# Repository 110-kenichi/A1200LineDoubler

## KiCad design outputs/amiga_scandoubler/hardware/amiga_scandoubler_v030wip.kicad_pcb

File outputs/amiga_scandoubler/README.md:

# Amiga 1200 15kHz → 31kHz スキャンダブラー

2026-09-29 / 全配線完了・製造データ一次版 v0.30 / **製造用リリースではありません（発注前の確認が残っている）**

## v0.30（最新）

- 変更点・検査結果・残作業：`revision_0.30.md`（作業ログは `revision_0.30wip.md`）
- 基板：`hardware/amiga_scandoubler_v030wip.kicad_pcb`（KiCad 7 形式。DRC エラー0・未接続0）
- 製造データ：`fab/v030wip/`（README に一覧と発注前の注意）
- 配線レビューとシミュレーション：`review_v030wip_wiring.md`
- ERC：`hardware/erc_k9.rpt`、除外 `hardware/erc_exclusions.json`

## v0.27 の内容（以下は当時の記述）

- **最新：出力側H/V同期配線**：`sync_out_review.md`
- 現行基板：`hardware/amiga_scandoubler_sync_out.kicad_pcb`
- 独立検査：`hardware/sync_out_report.json`、`hardware/sync_out_drc.txt`
- 配線図：`sync_out_review.png`、`sync_out_detail.png`

- v0.26：DACのRGB出力接続：`rgb_out_review.md`
- v0.26基板：`hardware/amiga_scandoubler_rgb_out.kicad_pcb`
- 検査：`hardware/rgb_out_report.json`、`hardware/rgb_out_drc.txt`
- 配線図：`rgb_out_review.png`、`rgb_out_detail.png`

- v0.25：PLLフィルター表面配線：`pll_top_review.md`
- v0.25基板：`hardware/amiga_scandoubler_pll_top.kicad_pcb`
- 独立検査：`hardware/pll_top_report.json`、`hardware/pll_top_drc.txt`
- 配線図：`pll_top_review.png`、`pll_top_detail.png`

- v0.24：R34付近の電源配線見直し：`r34_review.md`
- v0.24基板：`hardware/amiga_scandoubler_refined.kicad_pcb`
- 検査：`hardware/refined_report.json`、`hardware/refined_drc.txt`
- 配線図：`refined_review.png`

- v0.23：アナログ信号の部分配線：`analog_review.md`
- v0.23基板：`hardware/amiga_scandoubler_analog.kicad_pcb`
- 独立検査：`hardware/analog_report.json`、`hardware/analog_drc.txt`
- 配線図：`analog_review.png`、`analog_detail.png`

- v0.22：主要ICへの電源分配：`distribution_review.md`
- v0.22基板：`hardware/amiga_scandoubler_distribution.kicad_pcb`
- 接続・間隔の検査：`hardware/distribution_report.json`、`hardware/distribution_drc.txt`
- 主要IC周辺の配線図：`distribution_detail.png`

- v0.21 電源部の部分配線：`power_routing_review.md`
- v0.21の部分配線基板：`hardware/amiga_scandoubler_routing.kicad_pcb`
- 電源部の拡大図：`power_routing_detail.png`
- 接続・DRC検査：`hardware/power_routing_report.json`、`hardware/power_routing_drc.txt`

- FPGA現行：出力リセット解除の同期化：`output_release_review.md`
- 現行実装・経路解析・再現手順：`implementation/output_release/`

- v0.19 DAC出力段同期化：`output_stage_review.md`
- v0.19の再合成・配置配線と解析：`implementation/output_stage/`

- 出力段追加前のDACタイミング調査：`dac_timing_review.md`
- 端子別の暫定条件と解析手順：`implementation/dac_timing_budget.json`、`implementation/analyze_dac_sdf.py`

- PLLを180度へ更新：`phase180_integration.md`
- 180度の再合成・配置配線・遅延解析：`implementation/phase180/`
- 更新後の試験：`system_phase180_report.txt`、`capture_phase180_current_report.txt`

- 旧90度設定の調査履歴：`capture_timing_review.md`
- 配置後52経路の暫定解析：`implementation/capture_timing_estimate.json`
- 90度／180度の機能試験：`capture_phase90_report.txt`、`capture_phase180_report.txt`

- FPGA配置配線の試行結果と検証限界：`implementation_review.md`
- 配置配線後の回路・ログ・周期制約・再現手順：`implementation/`

- 基板トップの合成・合成後リセット検証：`board_synthesis.md`
- 合成後接続の照合：`board_netlist_audit.txt`、`synthesis/board_summary.json`
- 合成後リセット試験：`mapped_reset_simulation_report.txt`

- 基板接続と端子修正：`board_integration.md`、`rtl/amiga_board_top.sv`
- 62信号の端子制約候補：`constraints/amiga_board_top.cst`、`constraints/board_port_map.json`
- 起動リセット候補と試験：`rtl/configuration_reset.sv`、`board_simulation_report.txt`

- 統合回路の合成結果：`system_synthesis.md`、`synthesis/system_summary.json`
- 1816/2048条件の合成手順・ログ・ネットリスト：`synthesis/system_*`

- 機能回路の全体接続：`system_integration.md`、`rtl/amiga_logic_core.sv`
- ADC起動から映像出力までの機能試験：`system_simulation_report.txt`

- PLL再起動と監視接続：`pll_restart.md`、`rtl/pll_restart_control.sv`、`rtl/clock_recovery_system.sv`
- 起動・復帰の試験記録：`pll_restart_simulation_report.txt`

- PLL設定・ADC入力レジスターの構成候補：`pll_capture.md`、`rtl/gowin_video_pll.sv`、`rtl/adc_rgb_capture.sv`
- 理想クロックによる取り込み試験：`capture_simulation_report.txt`

- 入力同期前段と映像処理への接続：`stream_input.md`、`rtl/stream_sync_frontend.sv`、`rtl/stream_input_video.sv`
- 前段・統合試験の記録：`stream_simulation_report.txt`

- ADCの36件の設定候補と起動統合：`adc_configuration.md`、`rtl/tvp7002_boot.sv`
- ADC起動統合の試験結果：`adc_boot_simulation_report.txt`

- クロック停止監視・DAC省電力制御の接続条件：`clock_integration.md`
- 監視回路と統合映像処理：`rtl/video_clock_guard.sv`、`rtl/supervised_video_core.sv`
- 新規試験結果：`clock_simulation_report.txt`

- RGB・HS・VSを整列した統合映像処理：`rtl/video_core.sv`
- 統合試験の結果：`video_simulation_report.txt`
- 専用RAMへの合成確認：`synthesis_review.md`、`synthesis/`

- 合意済み仕様と回路構成案：`design.md`
- 編集可能なKiCad 7回路図（6機能シート）：`hardware/amiga_scandoubler.kicad_sch`
- 閲覧用の回路図（7ページ）：`schematic_review.pdf`
- 135部品・129接続の定義：`hardware/circuit_manifest.json`
- FPGAの仮端子割り当て：`hardware/fpga_pin_assignment.json`
- KiCad出力ネットリスト：`hardware/amiga_scandoubler.net`
- 接続照合の結果：`hardware/connectivity_report.txt`
- この版の変更点と残作業：`revision_0.27.md`
- 95×95mm・全135部品の配置基板：`hardware/amiga_scandoubler_placement.kicad_pcb`（未配線）
- 配置図：`placement_review.png`、`placement_review.svg`
- パッド接続・部品外形の照合：`hardware/placement_report.json`
- FPGA・ADCの専用フットプリント：`hardware/Amiga.pretty/`
- フットプリントの確認記録：`hardware/footprint_review.md`
- ADC起動制御・I²C通信：`rtl/adc_power_sequence.sv`、`rtl/i2c_register_write.sv`
- 制御系の接続条件：`control_interface.md`、試験結果：`control_simulation_report.txt`
- メーカー資料に基づく入力回路・端子接続案：`input_circuit.md`
- 主要部品の選定・調達確認状況：`parts_review.md`
- ライン倍化のSystemVerilog処理核：`rtl/line_double.sv`
- フィールド単位の出力同期処理核：`rtl/field_sync.sv`
- 自動照合付きシミュレーション：`sim/`、実行結果：`simulation_report.txt`
- 実機での確認項目と製造データの完成条件：`verification.md`

現在のコードは、ADC起動から映像出力までの機能回路を接続した**検証版**です。基板トップと実PLL・DDR出力の接続候補を追加しましたが、実入力設定、DACタイミング、端子の実配置まで検証した製品用FPGAデータではありません。

回路図と4層基板は検討版です。現行基板には電源部の部分配線と内層GND面がありますが、未接続160件とシルクの問題が残り、基板全体のDRCは合格していません。ガーバー、完成BOM、CPL、書き込み用ビットストリームは未作成です。フットプリントには寸法・実装条件の確認が残るものがあります。この版をJLCPCBに提出しないでください。

KiCadで開くときは`hardware`フォルダーをまとめて展開し、`amiga_scandoubler.kicad_sch`を開いてください。子シートとローカルシンボルも同梱しています。接続検査はKiCadが実際に出力したデータを照合しました。ERC、基板DRC、基板全体の合成・配置配線、実機試験の合格を意味するものではありません。

## 合意済み条件

Amiga 1200、所有済みのUNBUFFERED VGA変換アダプター、BENQ GW2780を使用。基板の入出力はいずれも3列15ピンDE-15メス。USB給電。15kHzのPAL/NTSCプログレッシブおよびインターレースを2倍の水平周波数に変換。インターレースはBob方式、各フィールドを1出力フレームにする。低遅延を優先し、外付けフレームメモリ・動き適応・フレームレート変換は搭載しない。

基板は100×100mm以内を目標とし、配線品質や実装性を優先する。今回の配置案は95×95mm。これは基板外形であり、コネクターや接続ケーブルを含む外形ではない。

## 検証の再実行

Python 3とIcarus Verilogを用意して、次を実行します。

```text
python sim/run_tests.py --bin-dir <Icarusのbinフォルダー> --report simulation_report.txt
python sim/run_control_tests.py --bin-dir <Icarusのbinフォルダー> --report control_simulation_report.txt
python sim/run_video_tests.py --bin-dir <Icarusのbinフォルダー> --report video_simulation_report.txt
python sim/run_clock_tests.py --bin-dir <Icarusのbinフォルダー> --report clock_simulation_report.txt
python sim/run_adc_boot_tests.py --bin-dir <Icarusのbinフォルダー> --report adc_boot_simulation_report.txt
python sim/run_stream_tests.py --bin-dir <Icarusのbinフォルダー> --report stream_simulation_report.txt
python sim/run_capture_tests.py --bin-dir <Icarusのbinフォルダー> --report capture_simulation_report.txt
python sim/run_pll_restart_tests.py --bin-dir <Icarusのbinフォルダー> --report pll_restart_simulation_report.txt
python sim/run_system_tests.py --bin-dir <Icarusのbinフォルダー> --report system_simulation_report.txt
python sim/run_board_tests.py --bin-dir <Icarusのbinフォルダー> --report board_simulation_report.txt
```

シミュレーションは処理核のデジタル動作を確認します。Amiga実機、アナログ画質、モニター互換性、FPGAへの実装可能性や実測遅延の確認ではありません。

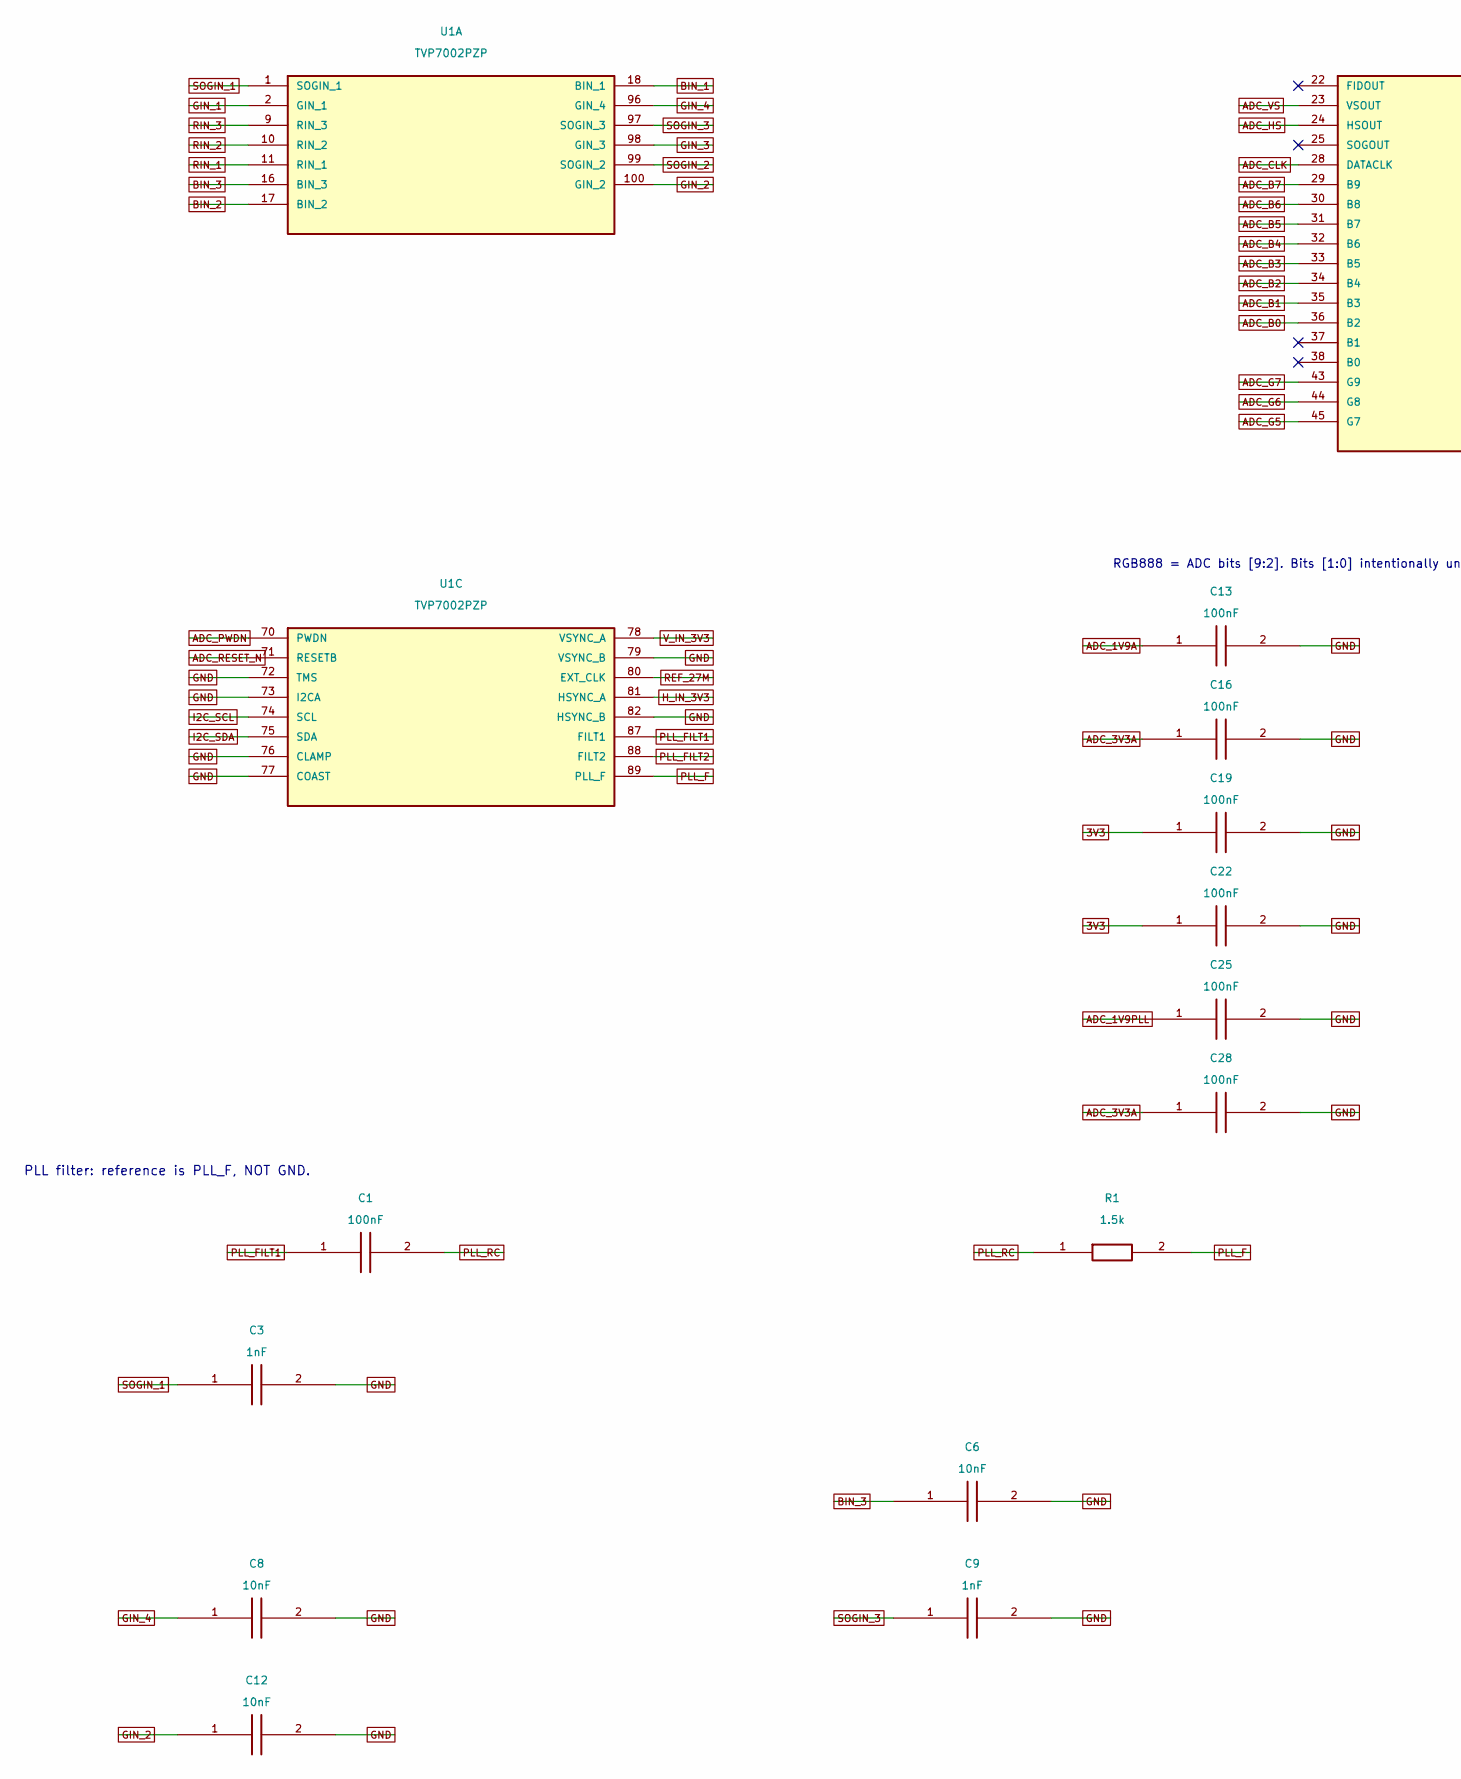
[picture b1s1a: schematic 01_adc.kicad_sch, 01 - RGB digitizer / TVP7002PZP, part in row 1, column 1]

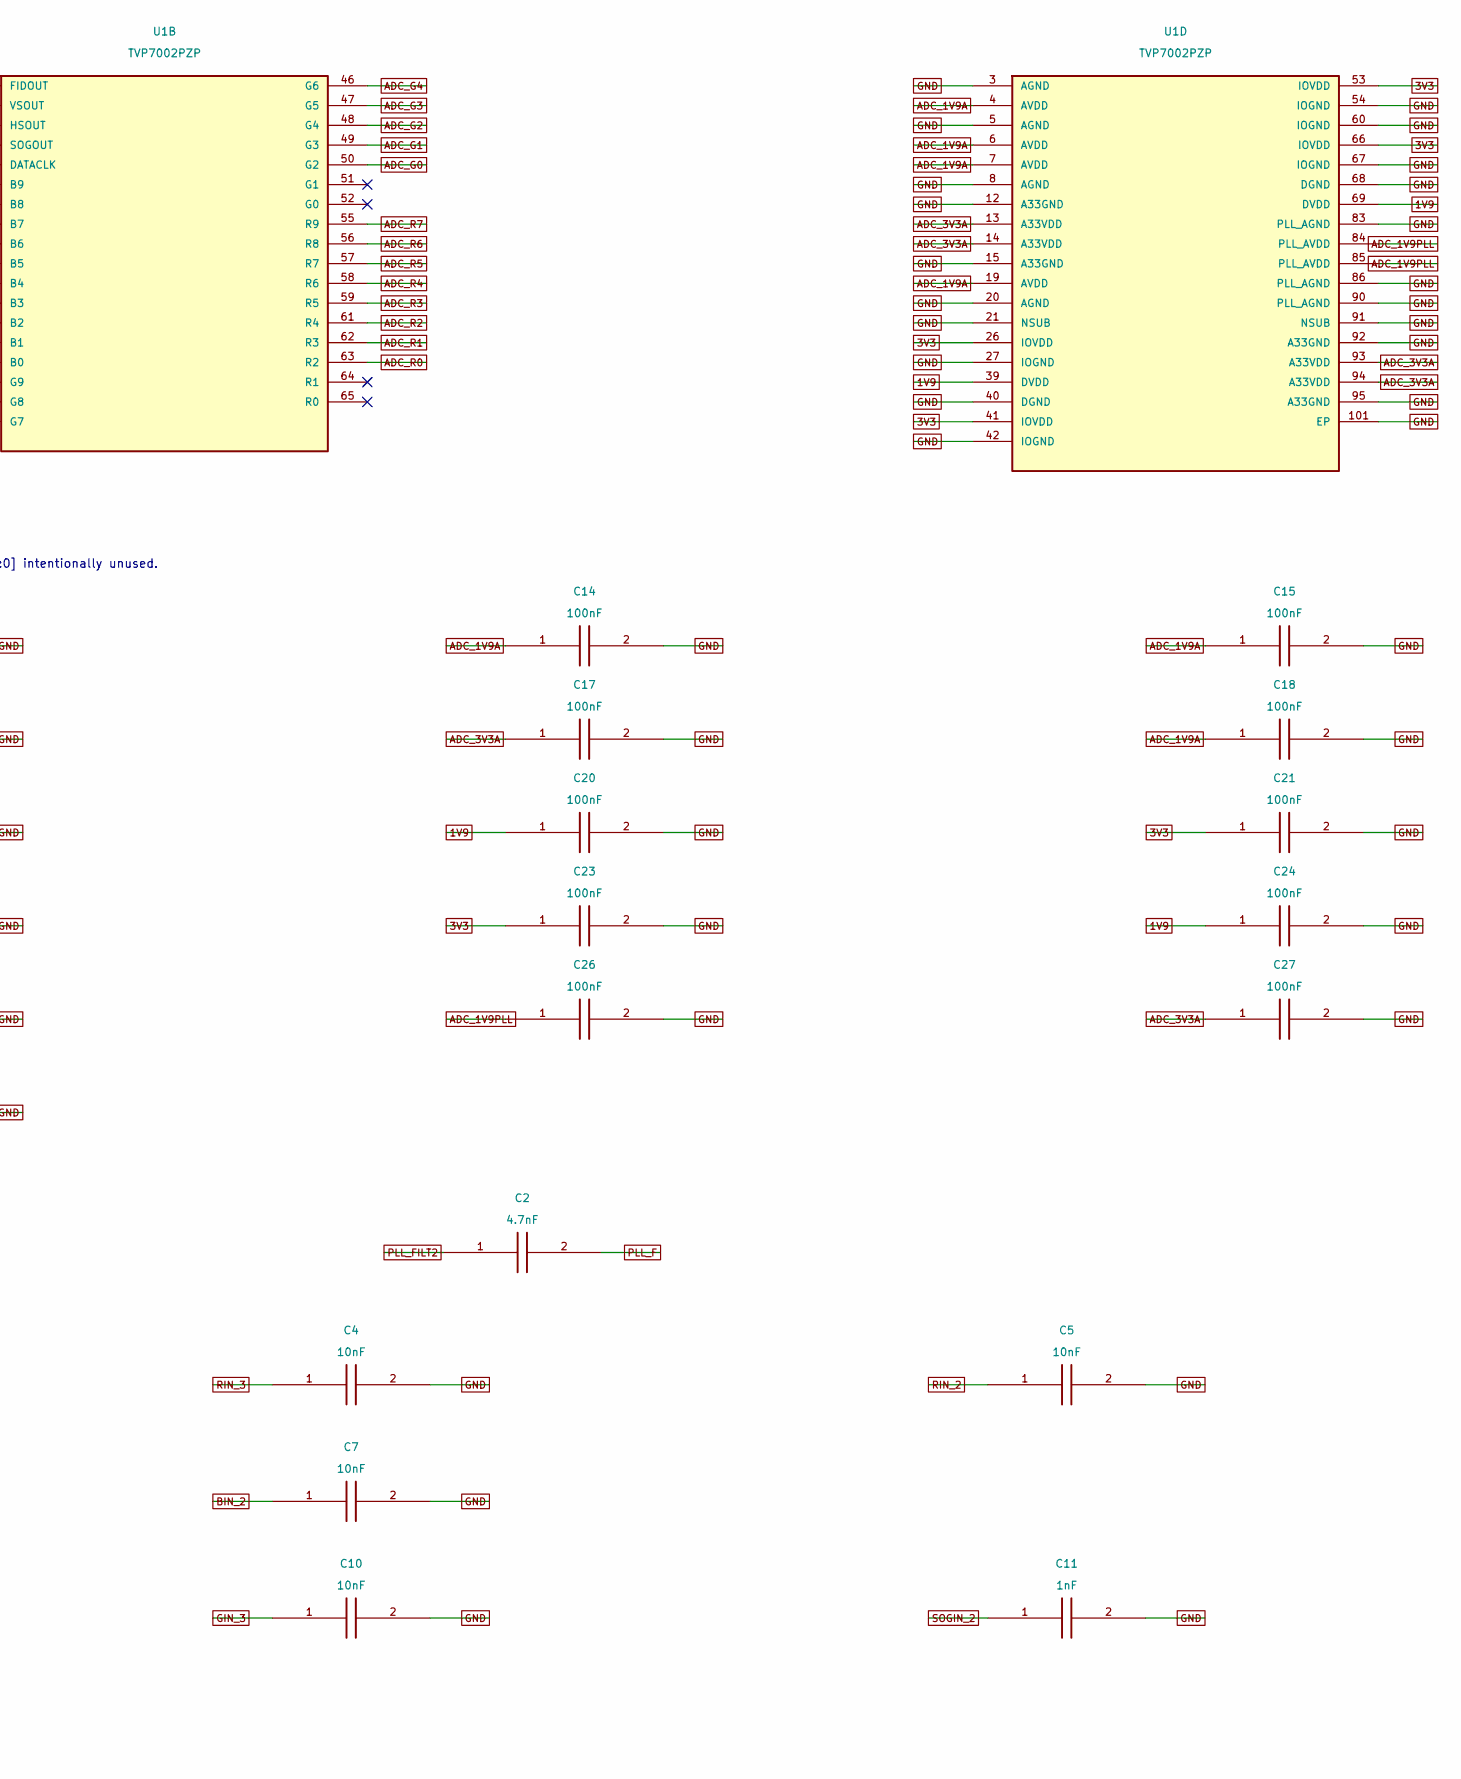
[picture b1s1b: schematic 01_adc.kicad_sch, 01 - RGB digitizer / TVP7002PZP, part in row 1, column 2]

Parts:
C1, C13, C14, C15, C16, C17, C18, C19, C20, C21, C22, C23, C24, C25, C26, C27, C28: 100nF; C_0603_1608Metric; MPN CC0603KRX7R9BB104; LCSC C14663
C2: 4.7nF; C_0603_1608Metric; MPN CC0603JRNPO9BN472; LCSC C576818
C3, C9, C11: 1nF; C_0603_1608Metric; MPN CC0603JRNPO9BN102; LCSC C106246
C4, C5, C6, C7, C8, C10, C12: 10nF; C_0603_1608Metric; MPN GRM1885C1H103JA01D; LCSC C85973
R1: 1.5k; R_0603_1608Metric; MPN 0603WAF1501T5E; LCSC C22843
U1: TVP7002PZP; TQFP-100_TVP7002_14x14_P0.5_EP6.2; MPN TVP7002PZP; LCSC C3824085

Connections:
1V9: C20.1, C24.1, U1.39 (DVDD), U1.69 (DVDD); also elsewhere on the board
3V3: C19.1, C21.1, C22.1, C23.1, U1.26 (IOVDD), U1.41 (IOVDD), U1.53 (IOVDD), U1.66 (IOVDD); also elsewhere on the board
ADC_1V9A: C13.1, C14.1, C15.1, C18.1, U1.4 (AVDD), U1.6 (AVDD), U1.7 (AVDD), U1.19 (AVDD); also elsewhere on the board
ADC_1V9PLL: C25.1, C26.1, U1.84 (PLL_AVDD), U1.85 (PLL_AVDD); also elsewhere on the board
ADC_3V3A: C16.1, C17.1, C27.1, C28.1, U1.13 (A33VDD), U1.14 (A33VDD), U1.93 (A33VDD), U1.94 (A33VDD); also elsewhere on the board
ADC_B0: U1.36 (B2); also elsewhere on the board
ADC_B1: U1.35 (B3); also elsewhere on the board
ADC_B2: U1.34 (B4); also elsewhere on the board
ADC_B3: U1.33 (B5); also elsewhere on the board
ADC_B4: U1.32 (B6); also elsewhere on the board
ADC_B5: U1.31 (B7); also elsewhere on the board
ADC_B6: U1.30 (B8); also elsewhere on the board
ADC_B7: U1.29 (B9); also elsewhere on the board
ADC_CLK: U1.28 (DATACLK); also elsewhere on the board
ADC_G0: U1.50 (G2); also elsewhere on the board
ADC_G1: U1.49 (G3); also elsewhere on the board
ADC_G2: U1.48 (G4); also elsewhere on the board
ADC_G3: U1.47 (G5); also elsewhere on the board
ADC_G4: U1.46 (G6); also elsewhere on the board
ADC_G5: U1.45 (G7); also elsewhere on the board
ADC_G6: U1.44 (G8); also elsewhere on the board
ADC_G7: U1.43 (G9); also elsewhere on the board
ADC_HS: U1.24 (HSOUT); also elsewhere on the board
ADC_PWDN: U1.70 (PWDN); also elsewhere on the board
ADC_R0: U1.63 (R2); also elsewhere on the board
ADC_R1: U1.62 (R3); also elsewhere on the board
ADC_R2: U1.61 (R4); also elsewhere on the board
ADC_R3: U1.59 (R5); also elsewhere on the board
ADC_R4: U1.58 (R6); also elsewhere on the board
ADC_R5: U1.57 (R7); also elsewhere on the board
ADC_R6: U1.56 (R8); also elsewhere on the board
ADC_R7: U1.55 (R9); also elsewhere on the board
ADC_RESET_N: U1.71 (RESETB); also elsewhere on the board
ADC_VS: U1.23 (VSOUT); also elsewhere on the board
BIN_1: U1.18 (BIN_1); also elsewhere on the board
BIN_2: C7.1, U1.17 (BIN_2)
BIN_3: C6.1, U1.16 (BIN_3)
GIN_1: U1.2 (GIN_1); also elsewhere on the board
GIN_2: C12.1, U1.100 (GIN_2)
GIN_3: C10.1, U1.98 (GIN_3)
GIN_4: C8.1, U1.96 (GIN_4)
GND: C3.2, C4.2, C5.2, C6.2, C7.2, C8.2, C9.2, C10.2, C11.2, C12.2, C13.2, C14.2, C15.2, C16.2, C17.2, C18.2, C19.2, C20.2, C21.2, C22.2, C23.2, C24.2, C25.2, C26.2, C27.2, C28.2, U1.3 (AGND), U1.5 (AGND), U1.8 (AGND), U1.12 (A33GND), U1.15 (A33GND), U1.20 (AGND), U1.21 (NSUB), U1.27 (IOGND), U1.40 (DGND), U1.42 (IOGND), U1.54 (IOGND), U1.60 (IOGND), U1.67 (IOGND), U1.68 (DGND), U1.72 (TMS), U1.73 (I2CA), U1.76 (CLAMP), U1.77 (COAST), U1.79 (VSYNC_B), U1.82 (HSYNC_B), U1.83 (PLL_AGND), U1.86 (PLL_AGND), U1.90 (PLL_AGND), U1.91 (NSUB), U1.92 (A33GND), U1.95 (A33GND), U1.101 (EP); also elsewhere on the board
H_IN_3V3: U1.81 (HSYNC_A); also elsewhere on the board
I2C_SCL: U1.74 (SCL); also elsewhere on the board
I2C_SDA: U1.75 (SDA); also elsewhere on the board
PLL_F: C2.2, R1.2, U1.89 (PLL_F)
PLL_FILT1: C1.1, U1.87 (FILT1)
PLL_FILT2: C2.1, U1.88 (FILT2)
PLL_RC: C1.2, R1.1
REF_27M: U1.80 (EXT_CLK); also elsewhere on the board
RIN_1: U1.11 (RIN_1); also elsewhere on the board
RIN_2: C5.1, U1.10 (RIN_2)
RIN_3: C4.1, U1.9 (RIN_3)
SOGIN_1: C3.1, U1.1 (SOGIN_1)
SOGIN_2: C11.1, U1.99 (SOGIN_2)
SOGIN_3: C9.1, U1.97 (SOGIN_3)
V_IN_3V3: U1.78 (VSYNC_A); also elsewhere on the board

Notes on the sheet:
RGB888 = ADC bits [9:2]. Bits [1:0] intentionally unused.
PLL filter: reference is PLL_F, NOT GND.

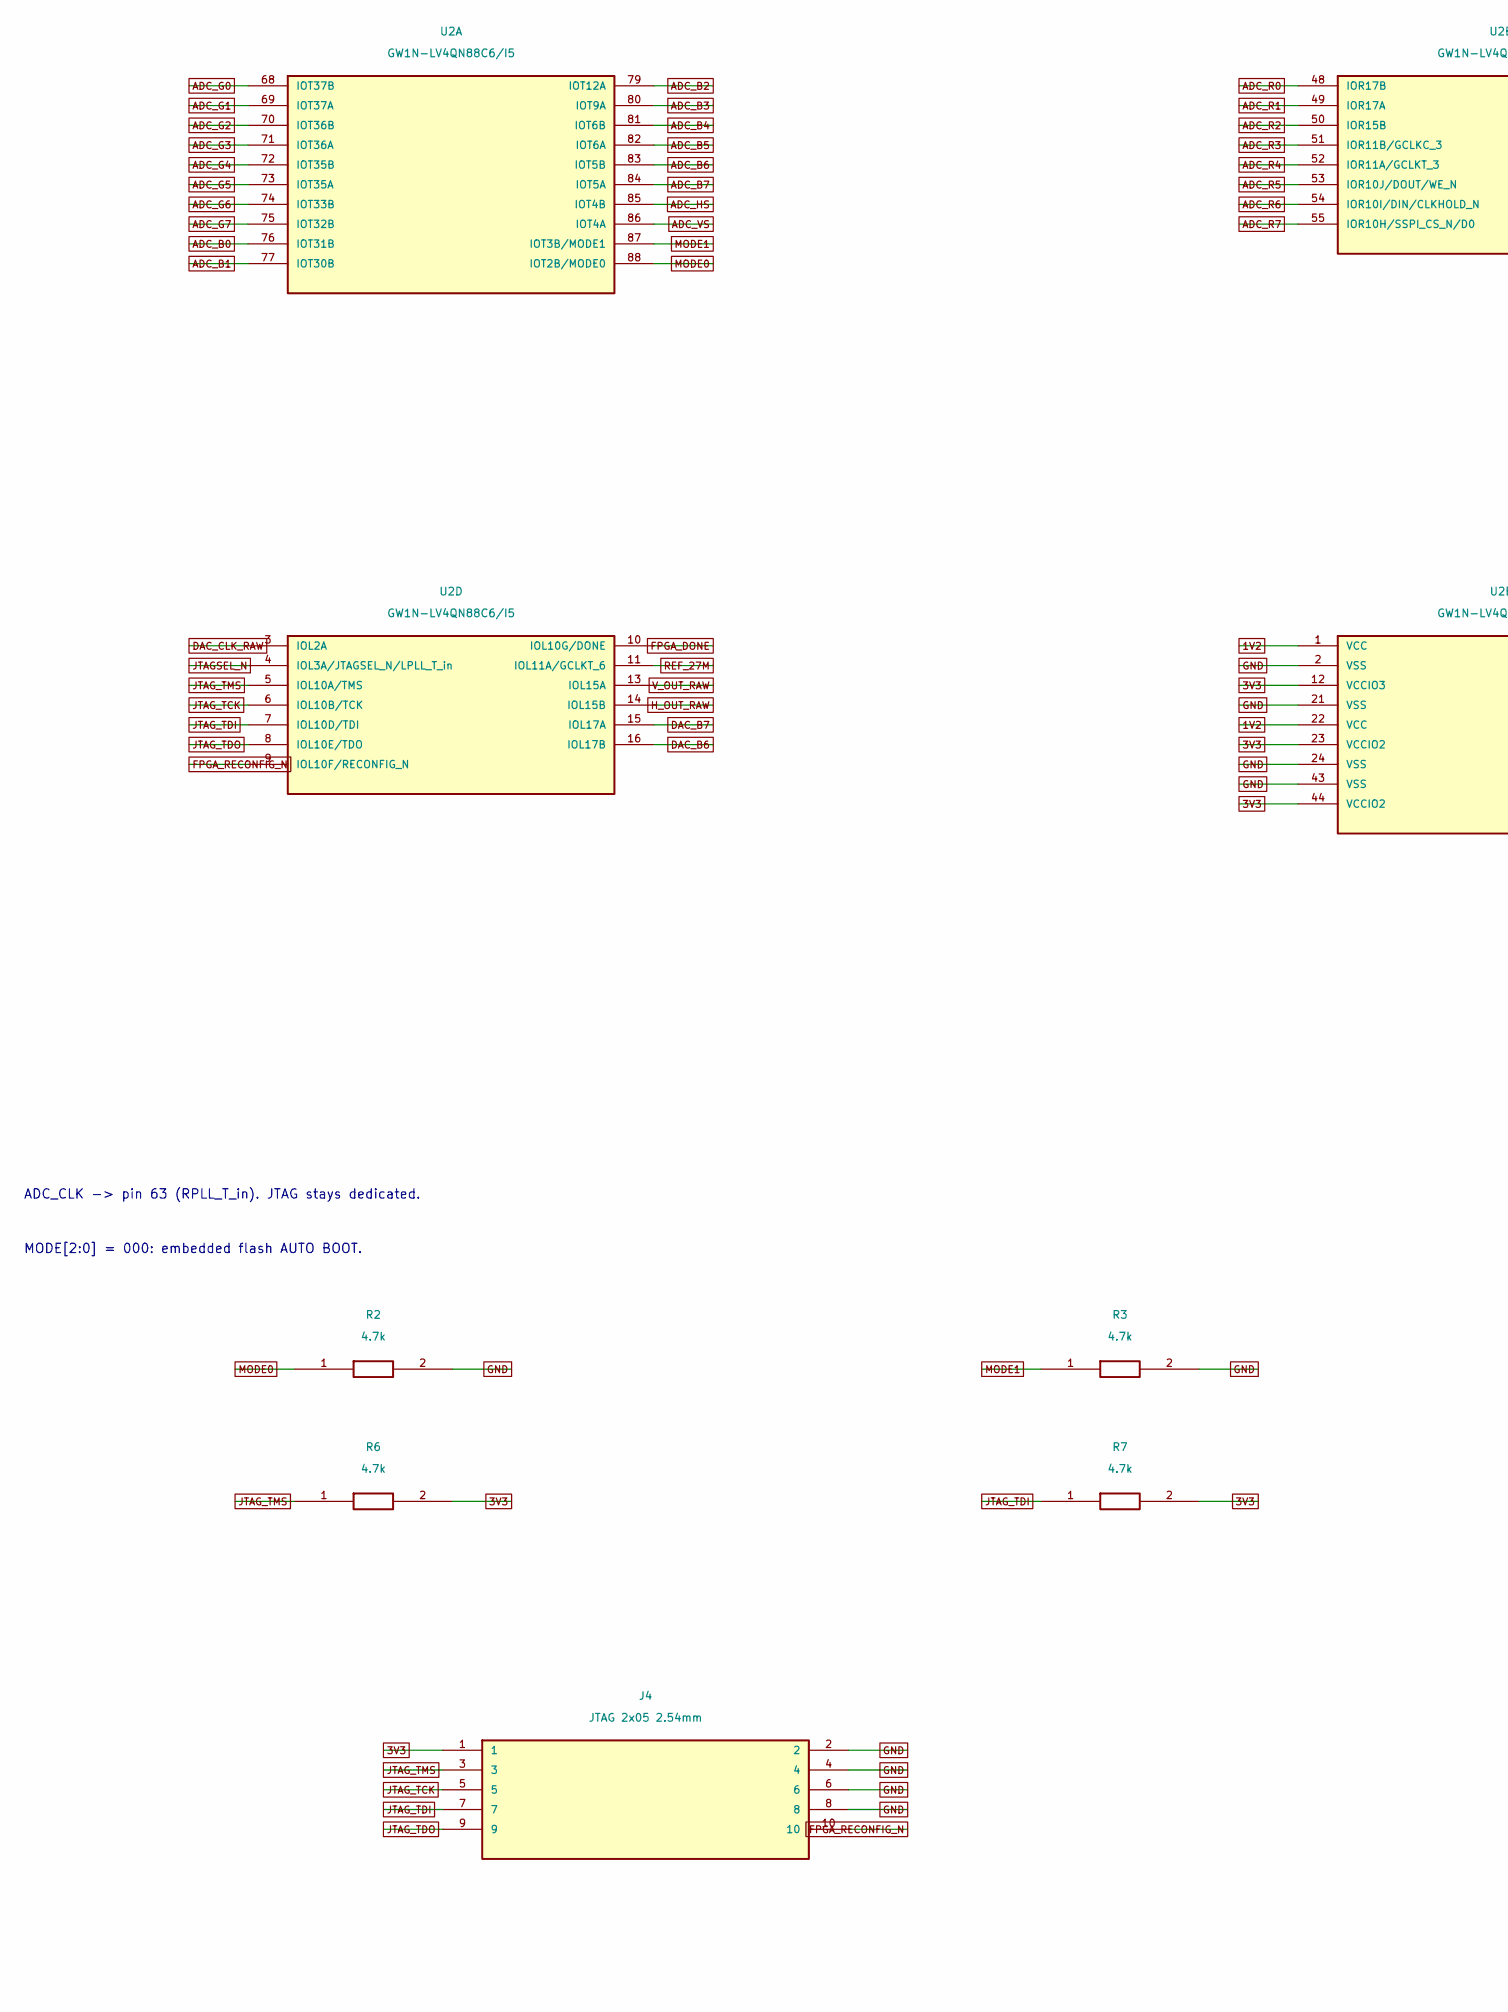
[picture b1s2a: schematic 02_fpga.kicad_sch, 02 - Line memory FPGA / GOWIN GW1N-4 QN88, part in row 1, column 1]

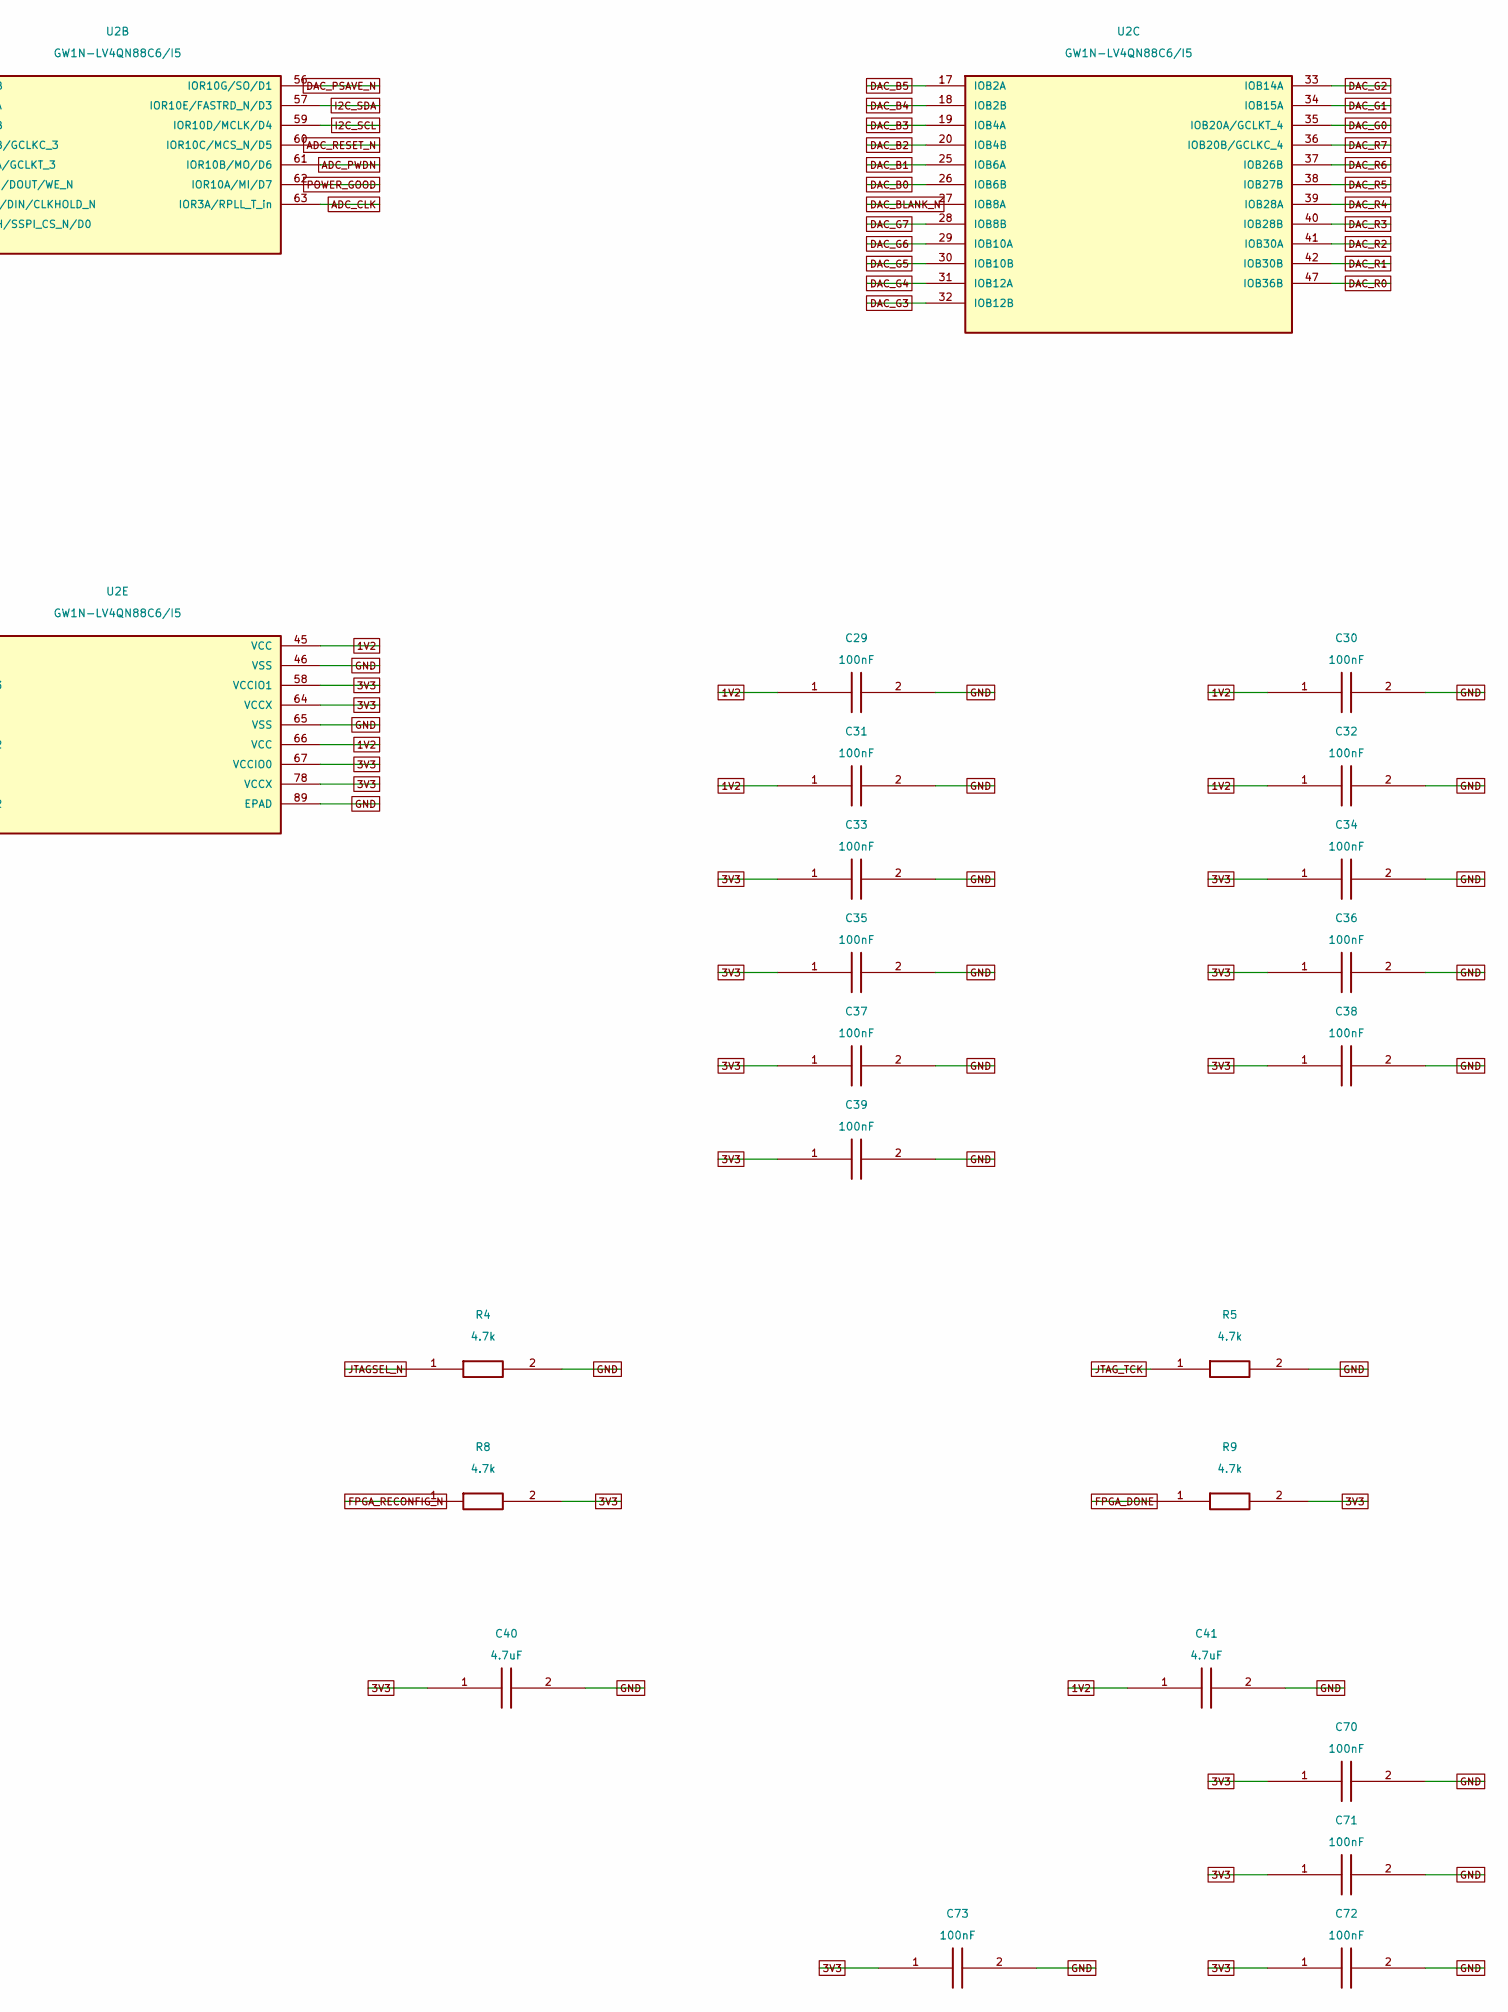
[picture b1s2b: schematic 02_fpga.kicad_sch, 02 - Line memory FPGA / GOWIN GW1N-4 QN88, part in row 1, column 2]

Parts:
C29, C30, C31, C32, C33, C34, C35, C36, C37, C38, C39: 100nF; C_0603_1608Metric; MPN CC0603KRX7R9BB104; LCSC C14663
C40, C41: 4.7uF; C_0805_2012Metric; MPN CL21A475KAQNNNE; LCSC C1779
C70, C71, C72, C73: 100nF; C_0402_1005Metric; MPN CL05B104KO5NNNC; LCSC C1525
J4: JTAG 2x05 2.54mm; PinHeader_2x05_P2.54mm_Vertical_SMD; MPN HX PZ2.54-2x5P TP; LCSC C32713285
R2, R3, R4, R5, R6, R7, R8, R9: 4.7k; R_0603_1608Metric; MPN 0603WAF4701T5E; LCSC C23162
U2: GW1N-LV4QN88C6/I5; QFN-88_GW1N4_10x10_P0.4_EP6.8; MPN GW1N-LV4QN88C6/I5; LCSC C31900351

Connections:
1V2: C29.1, C30.1, C31.1, C32.1, C41.1, U2.1 (VCC), U2.22 (VCC), U2.45 (VCC), U2.66 (VCC); also elsewhere on the board
3V3: C33.1, C34.1, C35.1, C36.1, C37.1, C38.1, C39.1, C40.1, C70.1, C71.1, C72.1, C73.1, J4.1, R6.2, R7.2, R8.2, R9.2, U2.12 (VCCIO3), U2.23 (VCCIO2), U2.44 (VCCIO2), U2.58 (VCCIO1), U2.64 (VCCX), U2.67 (VCCIO0), U2.78 (VCCX); also elsewhere on the board
ADC_B0: U2.76 (IOT31B); also elsewhere on the board
ADC_B1: U2.77 (IOT30B); also elsewhere on the board
ADC_B2: U2.79 (IOT12A); also elsewhere on the board
ADC_B3: U2.80 (IOT9A); also elsewhere on the board
ADC_B4: U2.81 (IOT6B); also elsewhere on the board
ADC_B5: U2.82 (IOT6A); also elsewhere on the board
ADC_B6: U2.83 (IOT5B); also elsewhere on the board
ADC_B7: U2.84 (IOT5A); also elsewhere on the board
ADC_CLK: U2.63 (IOR3A/RPLL_T_in); also elsewhere on the board
ADC_G0: U2.68 (IOT37B); also elsewhere on the board
ADC_G1: U2.69 (IOT37A); also elsewhere on the board
ADC_G2: U2.70 (IOT36B); also elsewhere on the board
ADC_G3: U2.71 (IOT36A); also elsewhere on the board
ADC_G4: U2.72 (IOT35B); also elsewhere on the board
ADC_G5: U2.73 (IOT35A); also elsewhere on the board
ADC_G6: U2.74 (IOT33B); also elsewhere on the board
ADC_G7: U2.75 (IOT32B); also elsewhere on the board
ADC_HS: U2.85 (IOT4B); also elsewhere on the board
ADC_PWDN: U2.61 (IOR10B/MO/D6); also elsewhere on the board
ADC_R0: U2.48 (IOR17B); also elsewhere on the board
ADC_R1: U2.49 (IOR17A); also elsewhere on the board
ADC_R2: U2.50 (IOR15B); also elsewhere on the board
ADC_R3: U2.51 (IOR11B/GCLKC_3); also elsewhere on the board
ADC_R4: U2.52 (IOR11A/GCLKT_3); also elsewhere on the board
ADC_R5: U2.53 (IOR10J/DOUT/WE_N); also elsewhere on the board
ADC_R6: U2.54 (IOR10I/DIN/CLKHOLD_N); also elsewhere on the board
ADC_R7: U2.55 (IOR10H/SSPI_CS_N/D0); also elsewhere on the board
ADC_RESET_N: U2.60 (IOR10C/MCS_N/D5); also elsewhere on the board
ADC_VS: U2.86 (IOT4A); also elsewhere on the board
DAC_B0: U2.26 (IOB6B); also elsewhere on the board
DAC_B1: U2.25 (IOB6A); also elsewhere on the board
DAC_B2: U2.20 (IOB4B); also elsewhere on the board
DAC_B3: U2.19 (IOB4A); also elsewhere on the board
DAC_B4: U2.18 (IOB2B); also elsewhere on the board
DAC_B5: U2.17 (IOB2A); also elsewhere on the board
DAC_B6: U2.16 (IOL17B); also elsewhere on the board
DAC_B7: U2.15 (IOL17A); also elsewhere on the board
DAC_BLANK_N: U2.27 (IOB8A); also elsewhere on the board
DAC_CLK_RAW: U2.3 (IOL2A); also elsewhere on the board
DAC_G0: U2.35 (IOB20A/GCLKT_4); also elsewhere on the board
DAC_G1: U2.34 (IOB15A); also elsewhere on the board
DAC_G2: U2.33 (IOB14A); also elsewhere on the board
DAC_G3: U2.32 (IOB12B); also elsewhere on the board
DAC_G4: U2.31 (IOB12A); also elsewhere on the board
DAC_G5: U2.30 (IOB10B); also elsewhere on the board
DAC_G6: U2.29 (IOB10A); also elsewhere on the board
DAC_G7: U2.28 (IOB8B); also elsewhere on the board
DAC_PSAVE_N: U2.56 (IOR10G/SO/D1); also elsewhere on the board
DAC_R0: U2.47 (IOB36B); also elsewhere on the board
DAC_R1: U2.42 (IOB30B); also elsewhere on the board
DAC_R2: U2.41 (IOB30A); also elsewhere on the board
DAC_R3: U2.40 (IOB28B); also elsewhere on the board
DAC_R4: U2.39 (IOB28A); also elsewhere on the board
DAC_R5: U2.38 (IOB27B); also elsewhere on the board
DAC_R6: U2.37 (IOB26B); also elsewhere on the board
DAC_R7: U2.36 (IOB20B/GCLKC_4); also elsewhere on the board
FPGA_DONE: R9.1, U2.10 (IOL10G/DONE)
FPGA_RECONFIG_N: J4.10, R8.1, U2.9 (IOL10F/RECONFIG_N)
GND: C29.2, C30.2, C31.2, C32.2, C33.2, C34.2, C35.2, C36.2, C37.2, C38.2, C39.2, C40.2, C41.2, C70.2, C71.2, C72.2, C73.2, J4.2, J4.4, J4.6, J4.8, R2.2, R3.2, R4.2, R5.2, U2.2 (VSS), U2.21 (VSS), U2.24 (VSS), U2.43 (VSS), U2.46 (VSS), U2.65 (VSS), U2.89 (EPAD); also elsewhere on the board
H_OUT_RAW: U2.14 (IOL15B); also elsewhere on the board
I2C_SCL: U2.59 (IOR10D/MCLK/D4); also elsewhere on the board
I2C_SDA: U2.57 (IOR10E/FASTRD_N/D3); also elsewhere on the board
JTAGSEL_N: R4.1, U2.4 (IOL3A/JTAGSEL_N/LPLL_T_in)
JTAG_TCK: J4.5, R5.1, U2.6 (IOL10B/TCK)
JTAG_TDI: J4.7, R7.1, U2.7 (IOL10D/TDI)
JTAG_TDO: J4.9, U2.8 (IOL10E/TDO)
JTAG_TMS: J4.3, R6.1, U2.5 (IOL10A/TMS)
MODE0: R2.1, U2.88 (IOT2B/MODE0)
MODE1: R3.1, U2.87 (IOT3B/MODE1)
POWER_GOOD: U2.62 (IOR10A/MI/D7); also elsewhere on the board
REF_27M: U2.11 (IOL11A/GCLKT_6); also elsewhere on the board
V_OUT_RAW: U2.13 (IOL15A); also elsewhere on the board

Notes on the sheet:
ADC_CLK -> pin 63 (RPLL_T_in). JTAG stays dedicated.
MODE[2:0] = 000: embedded flash AUTO BOOT.
